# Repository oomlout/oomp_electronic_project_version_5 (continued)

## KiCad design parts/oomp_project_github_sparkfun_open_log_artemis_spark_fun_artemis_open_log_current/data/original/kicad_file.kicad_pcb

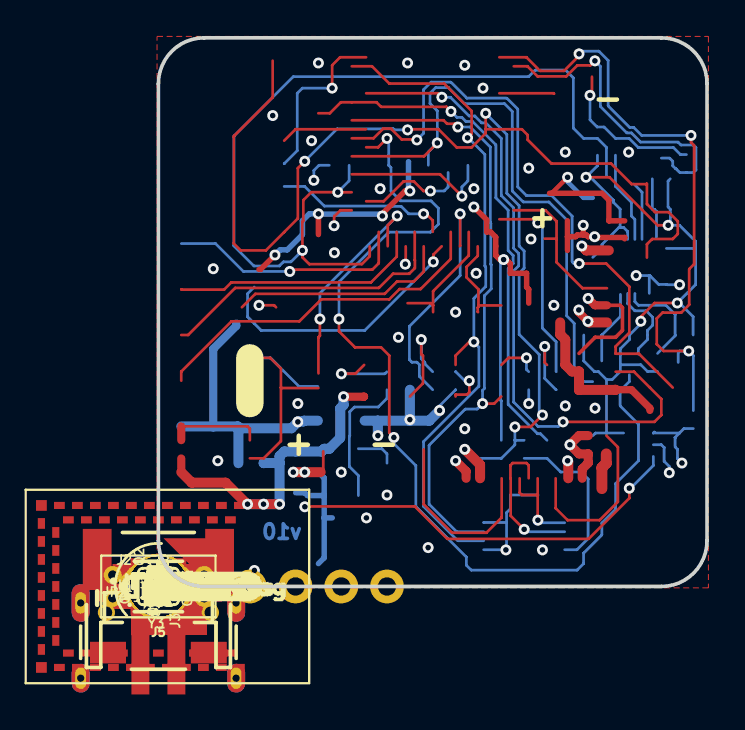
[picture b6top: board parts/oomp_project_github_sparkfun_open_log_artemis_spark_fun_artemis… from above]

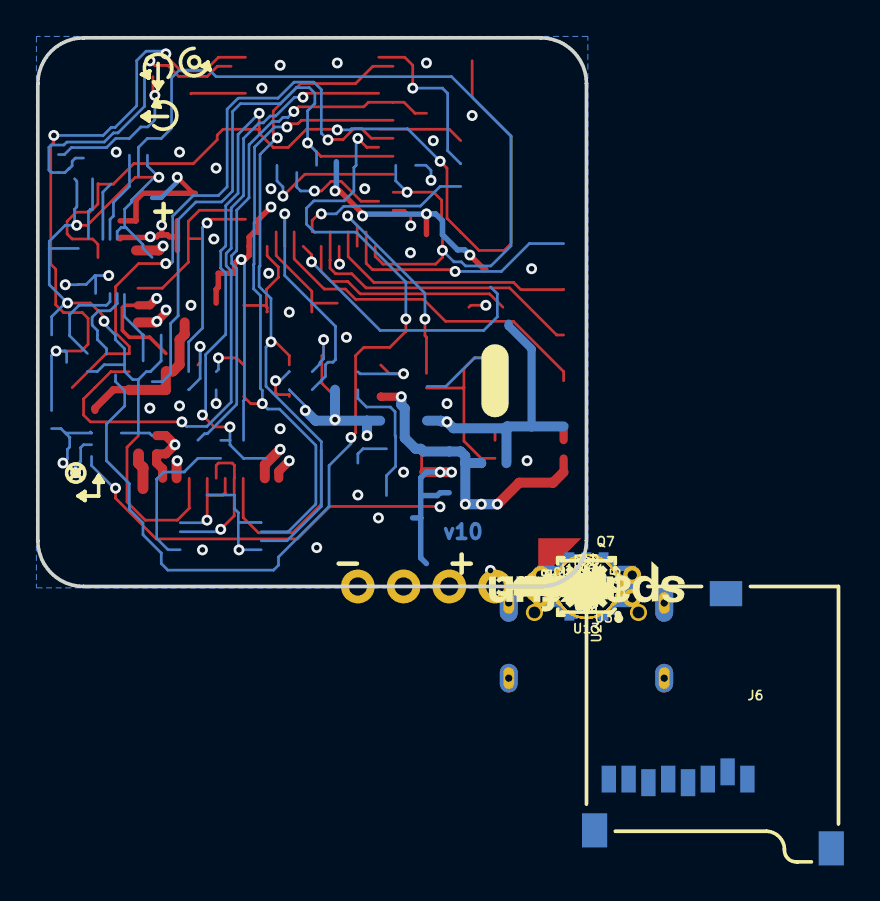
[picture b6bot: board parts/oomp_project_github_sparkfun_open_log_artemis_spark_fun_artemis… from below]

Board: 4 copper layers, 30.5 x 30.5 mm, 140 parts (74 on the bottom side), 61 nets.

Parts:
BT1: ML414H; ML414H_IV01E
C1, C33, C53, C54: 1.0uF; 0402-TIGHT
C2, C7: 2.2uF; 0402-TIGHT
C3, C4: 4.7uF; 0402-TIGHT
C5, C31, C41, C42, C43, C46, C51, C52: 0.1uF; 0402-TIGHT
C29, C30: 15pF; 0402-TIGHT
C32: 10uF; 0402-TIGHT
C40: 10nF; 0402-TIGHT
C44: 1.0nF; 0402-TIGHT
D1, D3: 3A/10V/280mV; SOD-323
D2, D11: Yellow; LED-0603
D6: 1A/23V/620mV; SOD-323
D9: BLUE; LED-0603
D12: GREEN; LED-0603
FD1, FD2, FD3, FD4: FIDUCIAL1X2; FIDUCIAL-1X2
FRAME1: FRAME-LEDGER; CREATIVE_COMMONS
GND0: TEST-POINTTP_15TH_THRU; TP_15TH
H1, H2, H3, H4: STAND-OFF
J1, J3: 1X02_NO_SILK
J2: JST-2-SMD
J4: 1X06_NO_SILK
J5: USB-C-16P_4LAYER-PADS
J6: MICRO-SD; MICRO-SD-SOCKET
J7: 1X01_NO_SILK
J11: QWIIC_RIGHT_ANGLE; JST04_1MM_RA
J14: CORTEX_JTAG; 2X5-PTH-1.27MM
JP2: MEAS; COMBO-JUMPER_2_NC_TRACE
LED1: RED; LED-0603
LOGO1: SFE_LOGO_NAME.1_INCH; SFE_LOGO_NAME_.1
LOGO2: OSHW-LOGOS; OSHW-LOGO-S
LOGO3: SPECIAL_INSTRUCTIONS-ORDERING; ORDERING_INSTRUCTIONS
LOGO4, LOGO5: SFE_LOGO_FLAME.1_INCH; SFE_LOGO_FLAME_.1
Q1, Q3, Q7, Q9, Q10: 20V/0.2A/8MHz/1.2Ω/1Vth; SOT-416FL
Q2: 20V/4.2A/52mΩ/1.4W; SOT23-3
QWIIC_3.3V0: TEST-POINTTP_15TH_THRU; TP_15TH
R1, R4, R40, R41, R44, R45, R46, R47, R48: 2.2k; 0402-TIGHT
R2: 330K; 0402-TIGHT
R3: 220k; 0402-TIGHT
R5, R22, R23, R24, R25: 1k; 0402-TIGHT
R6: 1M; 0402-TIGHT
R7: 2M; 0402-TIGHT
R8: 0; 0402-TIGHT
R26, R27: 5.1k; 0402-TIGHT
R28: 100k; 0402-TIGHT
R29: 220KOHM-0402T-1/16W-1%; 0402-TIGHT
R49: DNP; 0402-TIGHT
S3: RESET; TACTILE_SWITCH_SMD_4.6X2.8MM
SCL0: TEST-POINTTP_15TH_THRU; TP_15TH
SDA0: TEST-POINTTP_15TH_THRU; TP_15TH
TP1: TEST-POINT3; PAD.03X.03
U1: 3.0V Supervisor; SOT23-3
U2: MCP73831; SOT23-5
U3, U4: 3.3V; SOT23-5
U8: ARTEMIS_MODULE; ARTEMIS_FP
U10: CH340E; MSOP10
U13: 9DoF IMU; QFN24-3X3-ICM-20948
U14: 1.8V/100mA; SC70
U$1: QWIIC#LOGO#JPG
U$2: CHG2
U$3: PWR0
U$4: RX4
U$5: STAT5
U$6: VE0
U$7: TX3
U$8, U$12: RST0
U$9: ARTEMIS13
U$10, U$11: PSWC0
U$13: C0
U$14: D0
U$15: 30
U$27: MEAS3
U$28: OPENLOG12
U$32: RST9
U$33: VIN8
U$34, U$35: 3V34
U$36, U$37: 113
U$38, U$39: 322
U$40, U$41: GND5
U$42, U$54: RX1
U$43, U$49: X0
U$44, U$50: Y1
U$45, U$51: Z2
U$46: G5
U$47: A4
U$48: M3
U$55, U$56: TX0
VE0: SMT-JUMPER_2_NO_SILK
Y3: 32.768kHz; CRYSTAL-SMD-3.2X1.5MM

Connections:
3.3V: C2.1, C40.1, C41.1, C54.1, D6.A, J4.5, J14.1, Q2.2, R24.2, R25.2, R45.2, R47.2, R49.2, U1.3, U3.5, U10.7, U10.10, U14.1
5V: C3.1, D1.C, D2.A, J5.VBUS1, J5.VBUS2, JP2.1, JP2.3, U2.4
ARTEMIS_BOOT: C43.2, R29.2, U8.BOOT
ARTEMIS_RX0: D11.C, U8.RXI-0, U10.8
ARTEMIS_SWDCK: J14.4, U8.SWDCK
ARTEMIS_SWDIO: J14.2, U8.SWDIO
ARTEMIS_TX0: D12.C, U8.TXO-0, U10.9
ARTEMIS_~AD11: J4.1, U8.~AD11
ARTEMIS_~AD12/TX1: J4.3, U8.~AD12
ARTEMIS_~AD13/RX1: J4.2, U8.~AD13
ARTEMIS_~AD32: J4.4, U8.~AD32
ARTEMIS_~RESET: C42.2, C44.1, J7.1, J14.10, R28.1, S3.3, S3.4, U8.~RST
ARTEMIS_~RTS: C42.1, C43.1, U10.4
CC3: J5.B5, R26.2
CC4: J5.A5, R27.2
CHG_LED: R5.1, U2.1
D+2: J5.A6, J5.B6, U10.1
D-2: J5.A7, J5.B7, U10.2
DAT1: J6.DAT1, U8.~D26
DAT2: J6.DAT2, U8.~D4
GND: BT1.-, C1.2, C2.2, C3.2, C4.2, C5.2, C7.2, C29.1, C30.1, C31.1, C32.2, C33.2, C40.2, C41.2, C44.2, C46.2, C51.2, C52.2, C53.2, C54.2, D9.C, GND0.P$1, J1.2, J2.1, J3.2, J4.6, J5.GND, J5.GND2, J6.CD1, J6.GND, J6.GND1, J6.GND3, J11.1, J14.3, J14.5, J14.9, LED1.C, R3.1, R4.1, R6.1, R8.1, R26.1, R27.1, R29.1, S3.1, S3.2, U1.1, U2.2, U3.2, U4.2, U8.GND@1, U8.GND@22, U8.GND@38, U8.GND@39, U8.GND@47, U8.GND@59, U10.3, U13.18, U13.20, U14.2
ICM-20948-LV_#_1.8V: C52.1, C53.1, Q1.1, Q3.1, Q7.1, Q9.1, Q10.1, R40.2, R41.2, R44.2, R46.2, R48.2, U13.8, U13.13, U14.5
ICM-20948-LV_INT: Q7.2, R44.1, U13.12
ICM-20948-LV_SCK: Q1.2, R40.1, U13.23
ICM-20948-LV_SDI: Q3.2, R41.1, U13.24
ICM-20948-LV_SDO: Q10.2, R48.1, U13.9
ICM-20948-LV_~CS: Q9.2, R46.1, U13.22
ICM_INT: Q7.3, R45.1, U8.~D37
ICM_PWR: U8.~D27, U14.3
ICM_~CS: Q9.3, R47.1, U8.~D44
MICROSD_PWR: Q2.1, U8.D15
MICROSD_~CS: J6.CS/DAT3, U8.~D23
unnamed: J5.SHLD1, J5.SHLD2, J5.SHLD3, J5.SHLD4, R8.2
unnamed: R4.2, U2.5
unnamed: D2.C, R5.2
unnamed: C29.2, U8.XO, Y3.P$2
unnamed: C30.2, U8.XI, Y3.P$1
unnamed: LED1.A, R22.1
unnamed: D9.A, R23.1
unnamed: D12.A, R25.1
unnamed: D11.A, R24.1
unnamed: C51.1, U13.10
PWR_LED: R22.2, U8.~AD29
QWIIC_3.3V: C5.1, C7.1, J11.2, QWIIC_3.3V0.P$1, U4.5
QWIIC_PWR: R3.2, U4.3, U8.~D18
RTC_BAT+: BT1.+, D3.A, R1.1, TP1.P$1
SCK: J6.SCLK, Q1.3, U8.~D5
SCL: J11.4, SCL0.P$1, U8.D8
SDA: J11.3, SDA0.P$1, U8.D9
SDI: J6.DO/DAT0, Q10.3, R49.1, U8.~D6, U8.~D22
SDO: J6.DI/CMD, Q3.3, U8.D7
SD_PWR: C46.1, J6.VCC, Q2.3
STATLED: R23.2, U8.~D19
SWO: J14.6, U8.~AD33/SWO
VCC_1: C31.2, C32.1, C33.1, D3.C, D6.C, R1.2, R28.2, U8.VDD@36, U8.VDD@37
VIN: C1.1, JP2.2, JP2.4, R2.2, R7.2, U3.1, U4.1
VIN/3: R6.2, R7.1, U8.AD34
VREG_EN: J3.1, R2.1, U3.3, VE0.2
VREG_EN1: U8.~D25, VE0.1
V_BATT: C4.1, D1.A, J1.1, J2.2, U2.3
~POWER_LOSS: U1.2, U8.D3

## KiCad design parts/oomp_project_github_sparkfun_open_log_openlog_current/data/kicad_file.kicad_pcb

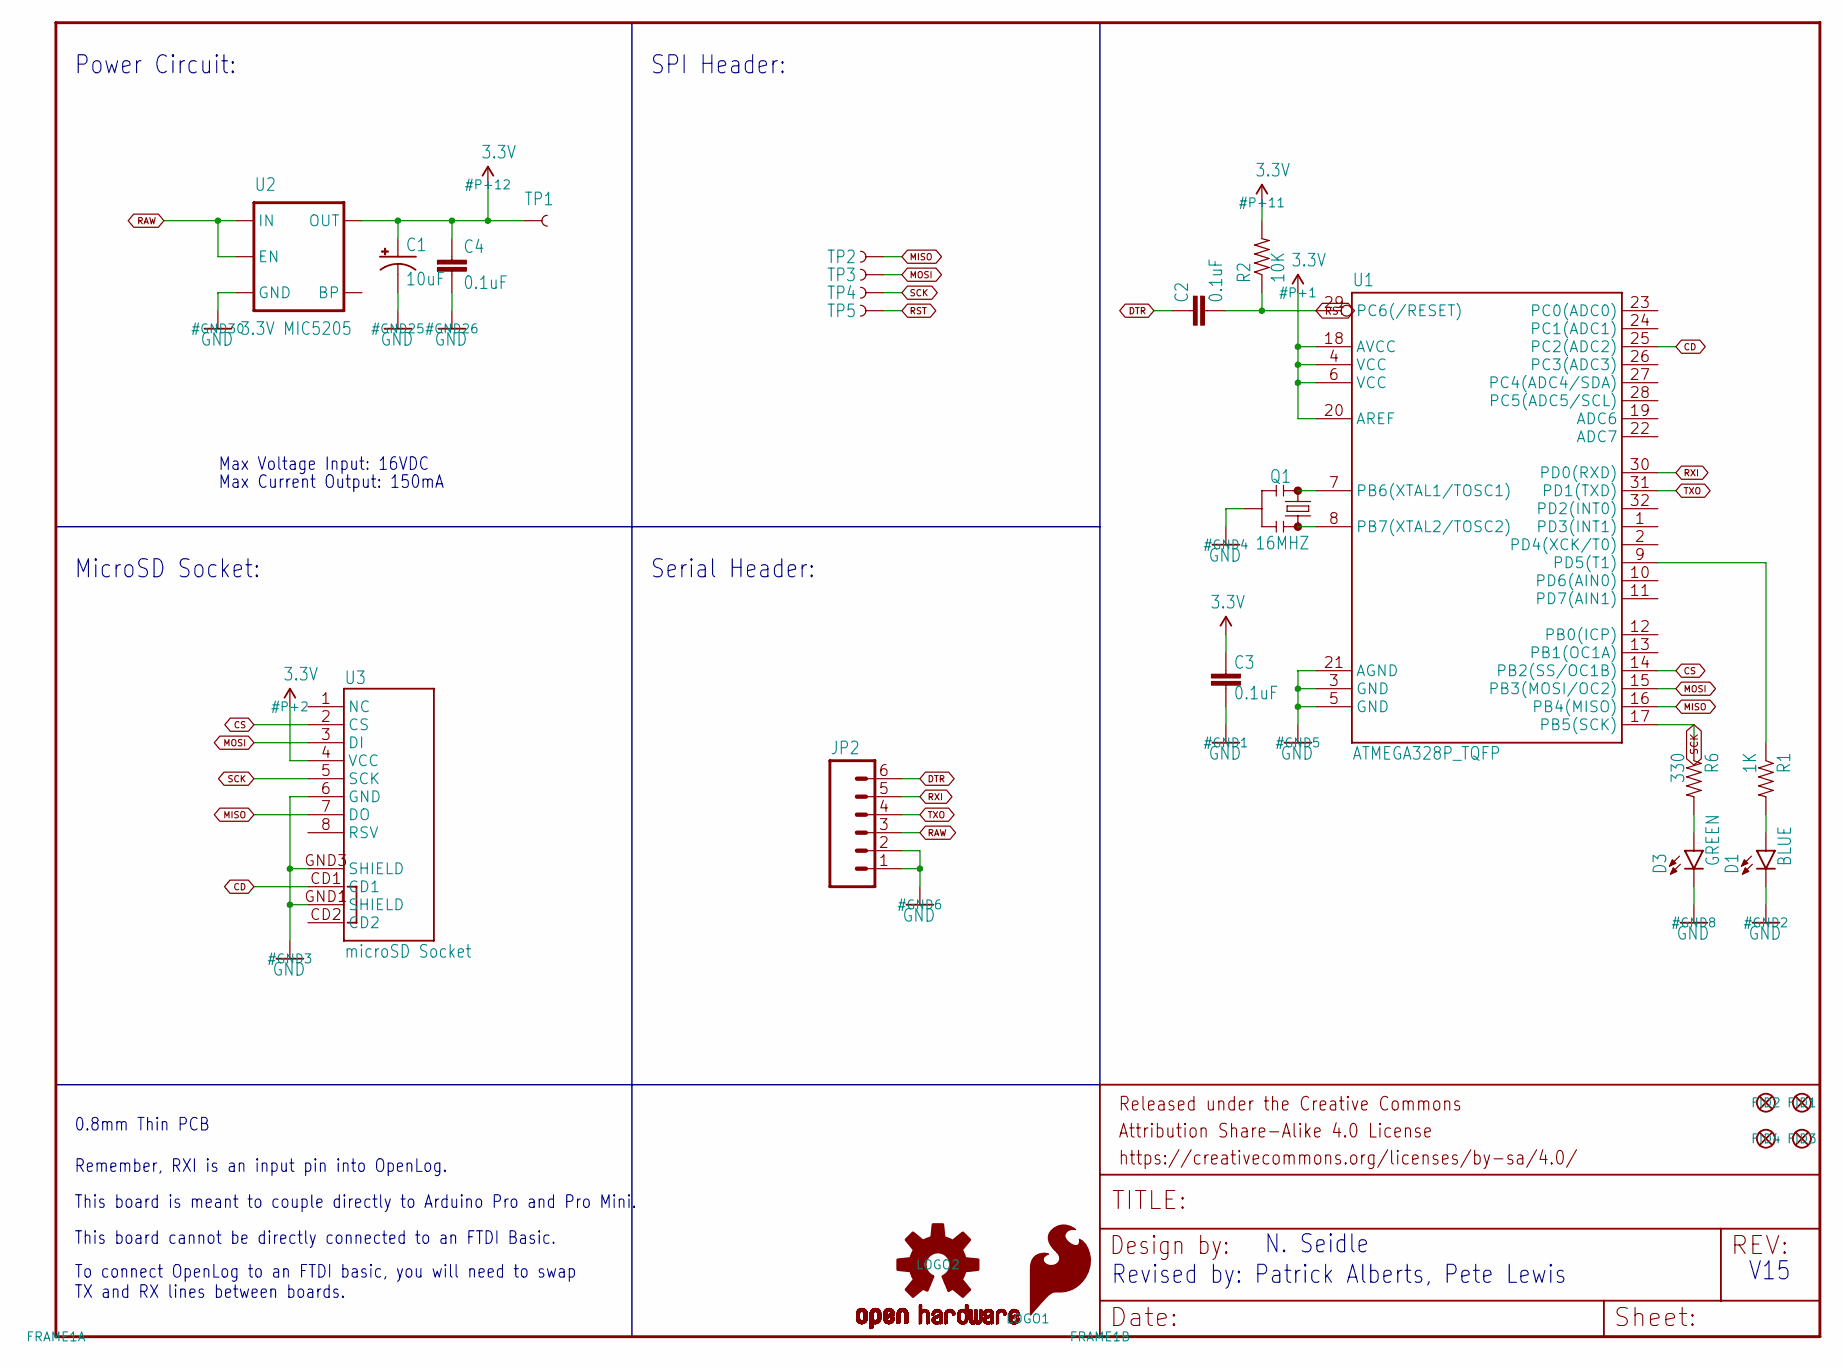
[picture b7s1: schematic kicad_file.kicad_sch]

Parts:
C1: 10uF; 0603-POL
C2, C3, C4: 0.1uF; 0603-CAP
D1: BLUE; LED-0603
D3: GREEN; LED-0603
FID1, FID2, FID3, FID4: FIDUCIALUFIDUCIAL; MICRO-FIDUCIAL
FRAME1: FRAME-LETTER; CREATIVE_COMMONS
JP2: M06NO_SILK_FEMALE_PTH; 1X06_NO_SILK
LOGO1: SFE_LOGO_FLAME.1_INCH; SFE_LOGO_FLAME_.1
LOGO2: OSHW-LOGOMINI; OSHW-LOGO-MINI
Q1: 16MHZ; RESONATOR-SMD
R1: 1K; 0603-RES
R2: 10K; 0603-RES
R6: 330; 0603-RES
TP1, TP2, TP3, TP4, TP5: TEST-POINT3; PAD.03X.03
U1: ATMEGA328P_TQFP; TQFP32-08
U2: 3.3V MIC5205; SOT23-5
U3: microSD Socket; MICROSD_1_1

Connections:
3.3V: C1.A (+), C3.2, C4.1, R2.2, TP1.P$1, U1.4 (VCC), U1.6 (VCC), U1.18 (AVCC), U1.20 (AREF), U2.5 (OUT), U3.4 (VCC)
CD: U1.25 (PC2(ADC2)), U3.CD1
CS: U1.14 (PB2(SS/OC1B)), U3.2 (CS)
DTR: C2.2, JP2.6
GND: C1.K (-), C3.1, C4.2, D1.C, D3.C, JP2.1, JP2.2, Q1.2, U1.3 (GND), U1.5 (GND), U1.21 (AGND), U2.2 (GND), U3.6 (GND), U3.GND1 (SHIELD), U3.GND3 (SHIELD)
MISO: TP2.P$1, U1.16 (PB4(MISO)), U3.7 (DO)
MOSI: TP3.P$1, U1.15 (PB3(MOSI/OC2)), U3.3 (DI)
unnamed: Q1.1, U1.8 (PB7(XTAL2/TOSC2))
unnamed: Q1.3, U1.7 (PB6(XTAL1/TOSC1))
unnamed: D1.A, R1.2
unnamed: R1.1, U1.9 (PD5(T1))
unnamed: D3.A, R6.2
RAW: JP2.3, U2.1 (IN), U2.3 (EN)
RST: C2.1, R2.1, TP5.P$1, U1.29 (PC6(/RESET))
RXI: JP2.5, U1.30 (PD0(RXD))
SCK: R6.1, TP4.P$1, U1.17 (PB5(SCK)), U3.5 (SCK)
TXO: JP2.4, U1.31 (PD1(TXD))

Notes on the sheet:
Serial Header:
This board is meant to couple directly to Arduino Pro and Pro Mini.
Power Circuit:
Max Voltage Input: 16VDC
Max Current Output: 150mA
V15
MicroSD Socket:
This board cannot be directly connected to an FTDI Basic.
N. Seidle
0.8mm Thin PCB
Remember, RXI is an input pin into OpenLog.
To connect OpenLog to an FTDI basic, you will need to swap TX and RX lines between boards.
SPI Header:
Revised by: Patrick Alberts, Pete Lewis

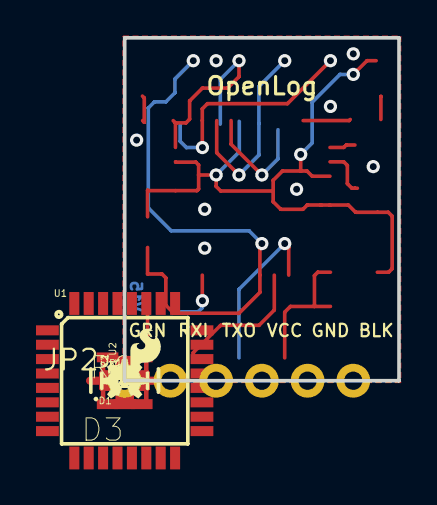
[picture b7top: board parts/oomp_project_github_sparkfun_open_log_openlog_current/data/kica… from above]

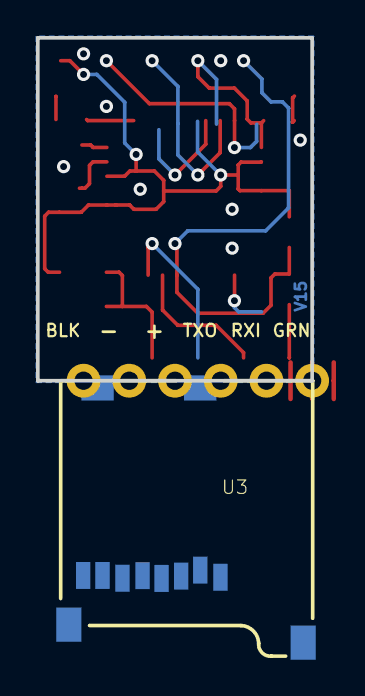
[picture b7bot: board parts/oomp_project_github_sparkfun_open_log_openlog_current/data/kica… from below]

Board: 2 copper layers, 15.2 x 19.1 mm, 26 parts (3 on the bottom side), 17 nets.

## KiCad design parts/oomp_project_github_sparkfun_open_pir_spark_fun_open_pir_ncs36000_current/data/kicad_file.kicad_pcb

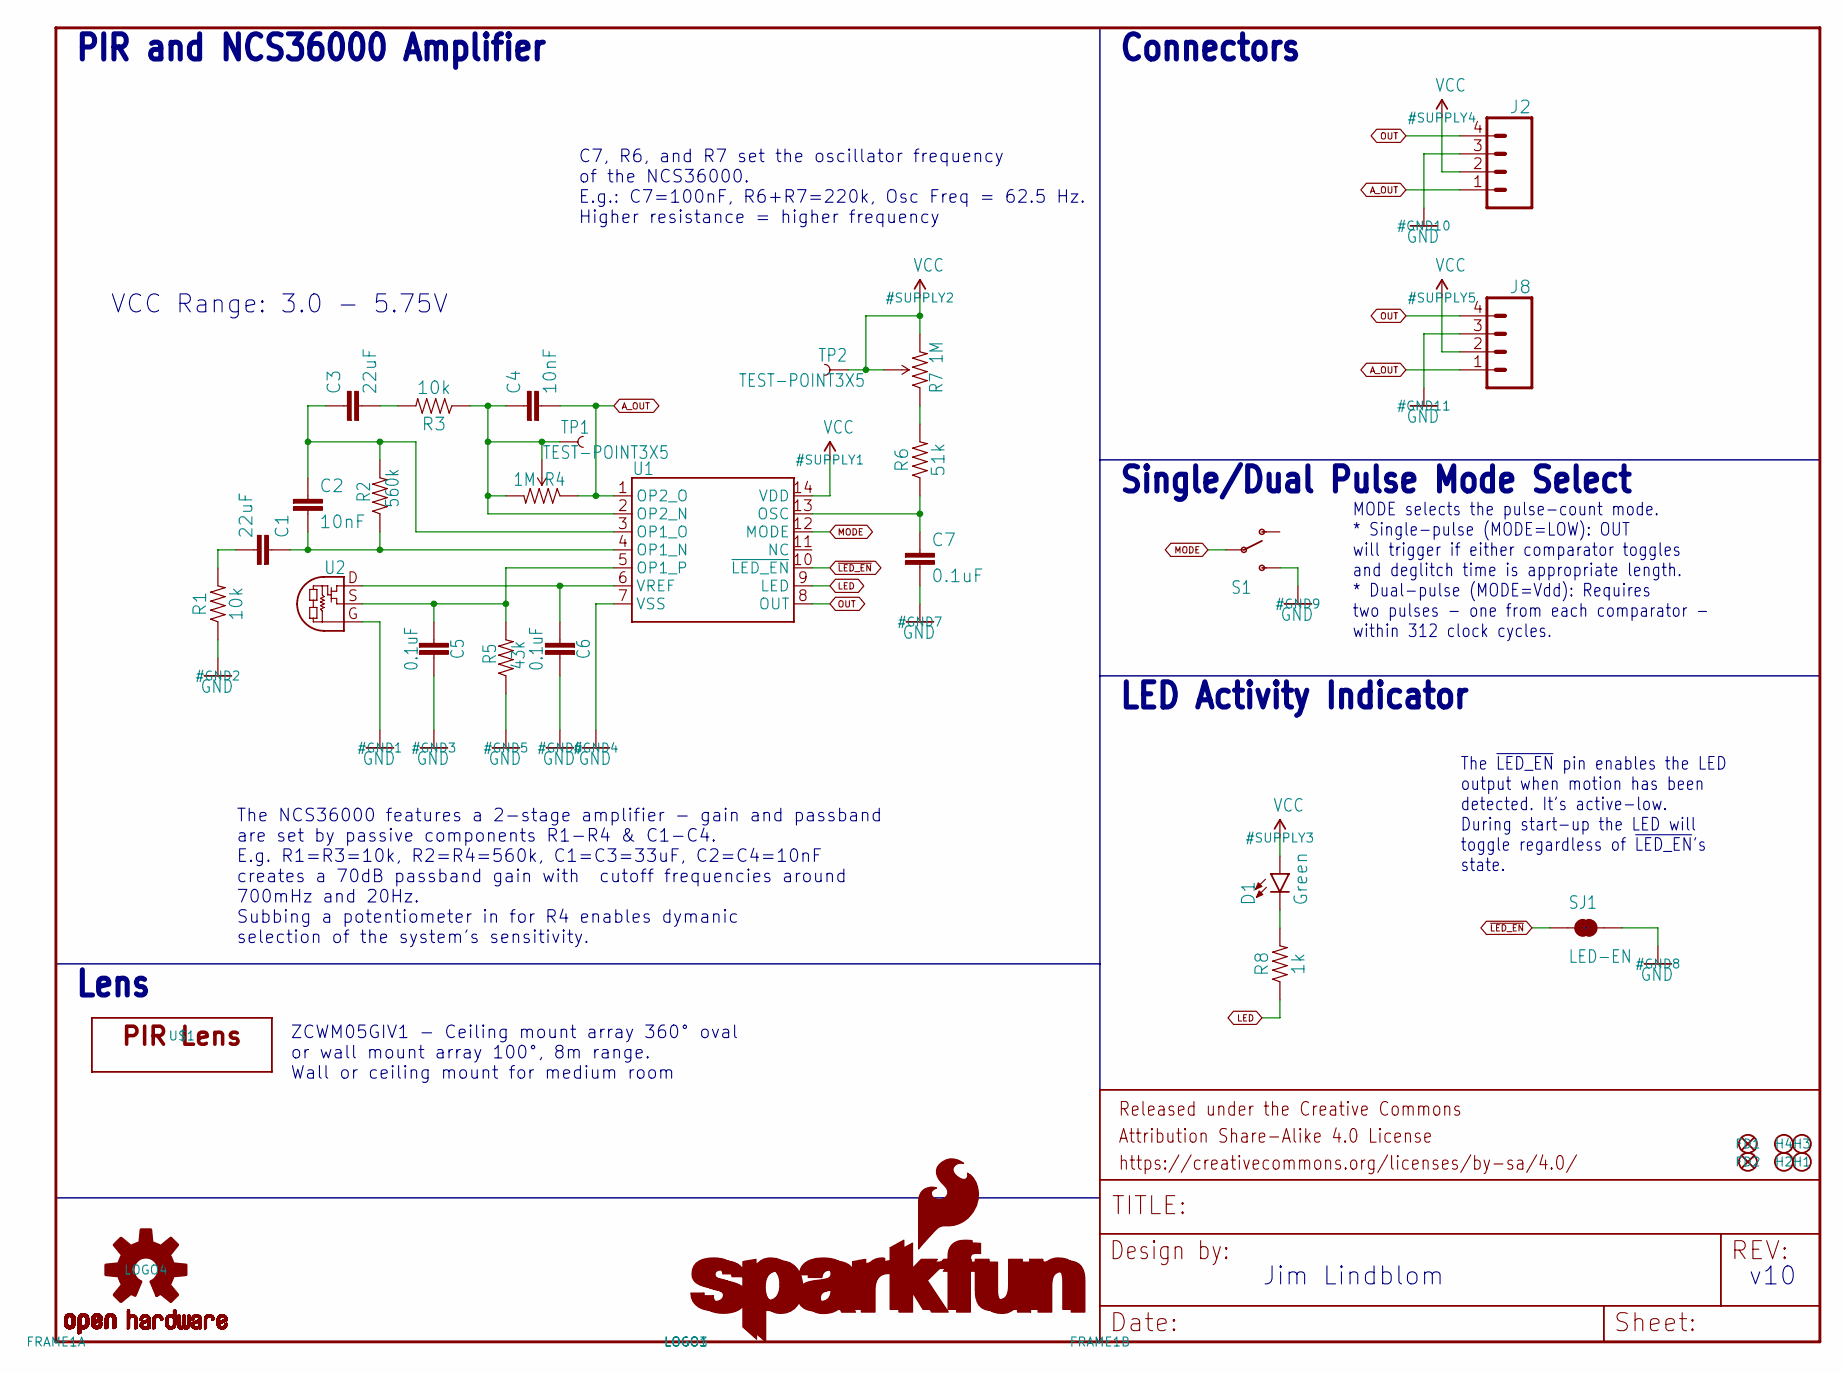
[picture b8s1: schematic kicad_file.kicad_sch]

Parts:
C1, C3: 22uF; 0805
C2, C4: 10nF; 0603
C5, C6, C7: 0.1uF; 0603
D1: Green; LED-1206-BOTTOM
FD1, FD2: FIDUCIALUFIDUCIAL; MICRO-FIDUCIAL
FRAME1: FRAME-LETTER; CREATIVE_COMMONS
H1, H2, H3, H4: STAND-OFF
J2: CONN_04JST-PTH-VERT-NS; JST-4-PTH-VERT-NS
J8: CONN_04NO_SILK_ALL_ROUND; 1X04_NO_SILK_ALL_ROUND
LOGO1: SFE_LOGO_NAME_FLAME.1_INCH; SFE_LOGO_NAME_FLAME_.1
LOGO3: SFE_LOGO_NAME.1_INCH; SFE_LOGO_NAME_.1
LOGO4: OSHW-LOGOS; OSHW-LOGO-S
R1, R3: 10k; 0603
R2: 560k; 0603
R4, R7: 1M; TRIMPOT-TC33X
R5: 43k; 0603
R6: 51k; 0603
R8: 1k; 0603
S1: SWITCH-SPDT-SMD-A; SWITCH-SPST-SMD-A
SJ1: LED-EN; SJ_2S
TP1, TP2: TEST-POINT3X5; PAD.03X.05
U1: NCS36000; SO14
U2: PIR
U$1: CWM 0.5 GI V1; LENS-CWM-0.5-GI-V1

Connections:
A_OUT: C4.2, J2.1, J8.1, R4.1 (CCW), U1.1 (OP2_O)
GND: C5.2, C6.2, C7.2, J2.3, J8.3, R1.1, R5.1, S1.3 (S), SJ1.2, U1.7 (VSS), U2.G
LED: R8.1, U1.9 (LED)
MODE: S1.2, U1.12 (MODE)
unnamed: C5.1, R5.2, U1.5 (OP1_P), U2.S
unnamed: C6.1, U1.6 (VREF), U2.D
unnamed: C1.2, R1.2
unnamed: C3.2, R3.2
unnamed: C1.1, C2.2, R2.1, U1.4 (OP1_N)
unnamed: C2.1, C3.1, R2.2, U1.3 (OP1_O)
unnamed: C4.1, R3.1, R4.2 (WIPER), R4.3 (CW), TP1.P$1, U1.2 (OP2_N)
unnamed: C7.1, R6.1, U1.13 (OSC)
unnamed: D1.C, R8.2
unnamed: R6.2, R7.1 (CCW)
OUT: J2.4, J8.4, U1.8 (OUT)
VCC: D1.A, J2.2, J8.2, R7.2 (WIPER), R7.3 (CW), TP2.P$1, U1.14 (VDD)
~LED_EN: SJ1.1, U1.10 (~LED_EN)

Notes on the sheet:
Lens
The ~{LED_EN} pin enables the LED output when motion has been detected. It's active-low. During start-up the LED will toggle regardless of ~{LED_EN}'s state.
Jim Lindblom
LED Activity Indicator
Connectors
v10
Single/Dual Pulse Mode Select
VCC Range: 3.0 - 5.75V
PIR and NCS36000 Amplifier
MODE selects the pulse-count mode. * Single-pulse (MODE=LOW): OUT will trigger if either comparator toggles and deglitch time is appropriate length. * Dual-pulse (MODE=Vdd): Requires two pulses - one from each comparator - within 312 clock cycles.
The NCS36000 features a 2-stage amplifier - gain and passband are set by passive components R1-R4 & C1-C4. E.g. R1=R3=10k, R2=R4=560k, C1=C3=33uF, C2=C4=10nF creates a 70dB passband gain with cutoff frequencies around 700mHz and 20Hz. Subbing a potentiometer in for R4 enables dymanic selection of t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
ZCWM05GIV1 - Ceiling mount array 360° oval or wall mount array 100°, 8m range. Wall or ceiling mount for medium room
C7, R6, and R7 set the oscillator frequency of the NCS36000. E.g.: C7=100nF, R6+R7=220k, Osc Freq = 62.5 Hz. Higher resistance = higher frequency

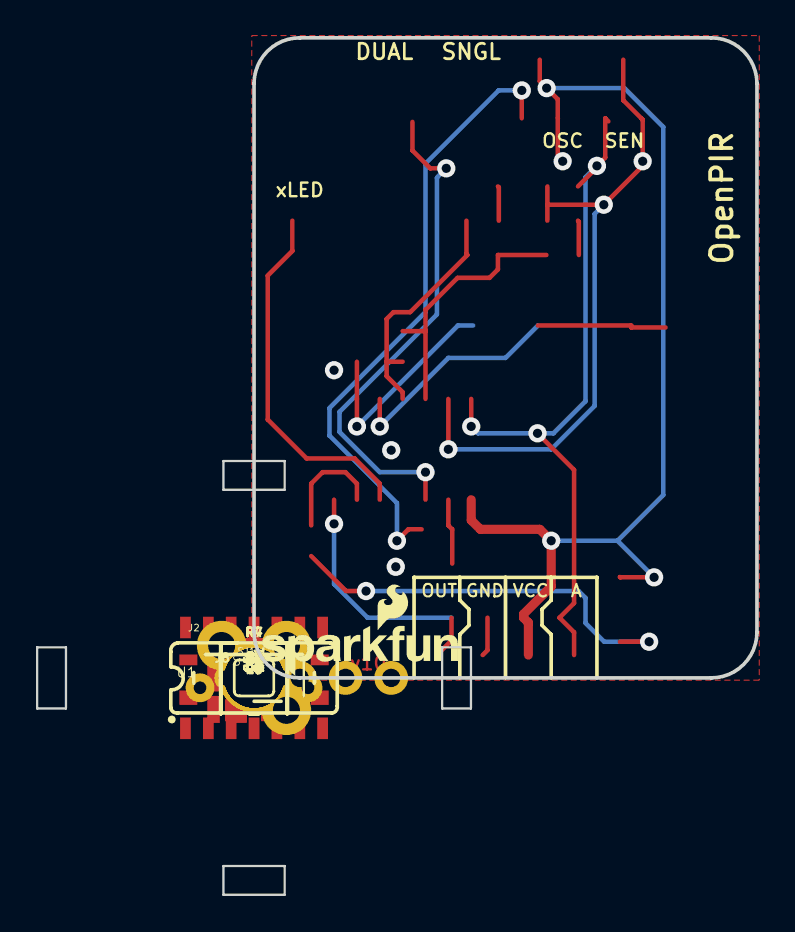
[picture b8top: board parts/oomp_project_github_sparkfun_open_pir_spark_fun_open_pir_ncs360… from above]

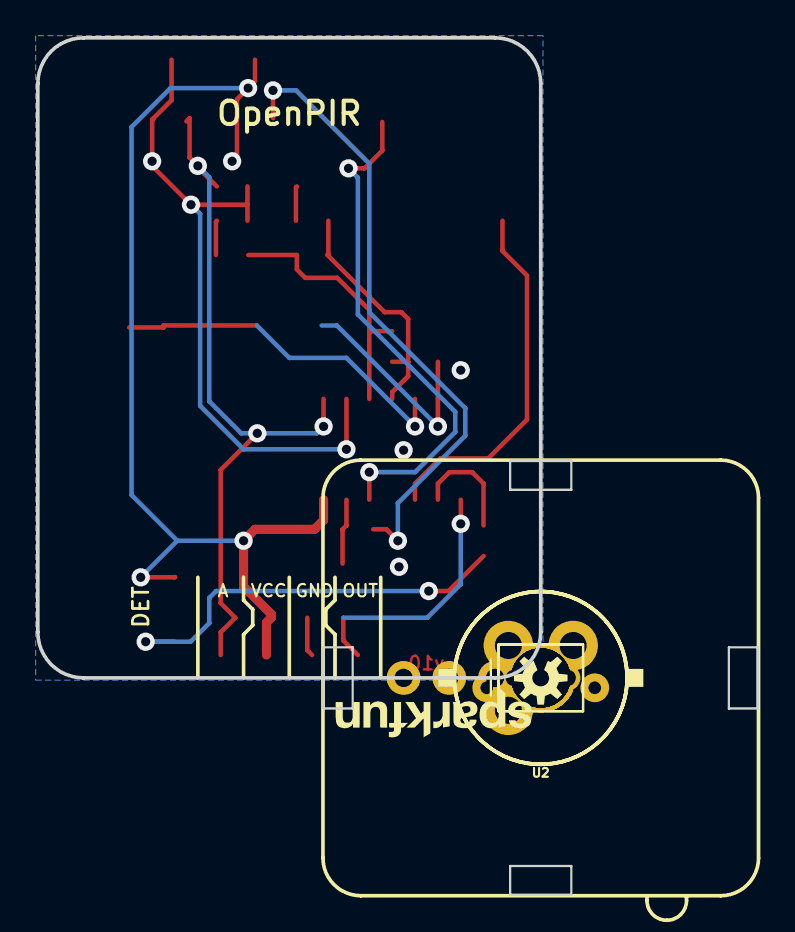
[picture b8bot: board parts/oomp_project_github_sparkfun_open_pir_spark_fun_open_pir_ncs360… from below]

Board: 2 copper layers, 27.9 x 35.6 mm, 35 parts (6 on the bottom side), 17 nets.
